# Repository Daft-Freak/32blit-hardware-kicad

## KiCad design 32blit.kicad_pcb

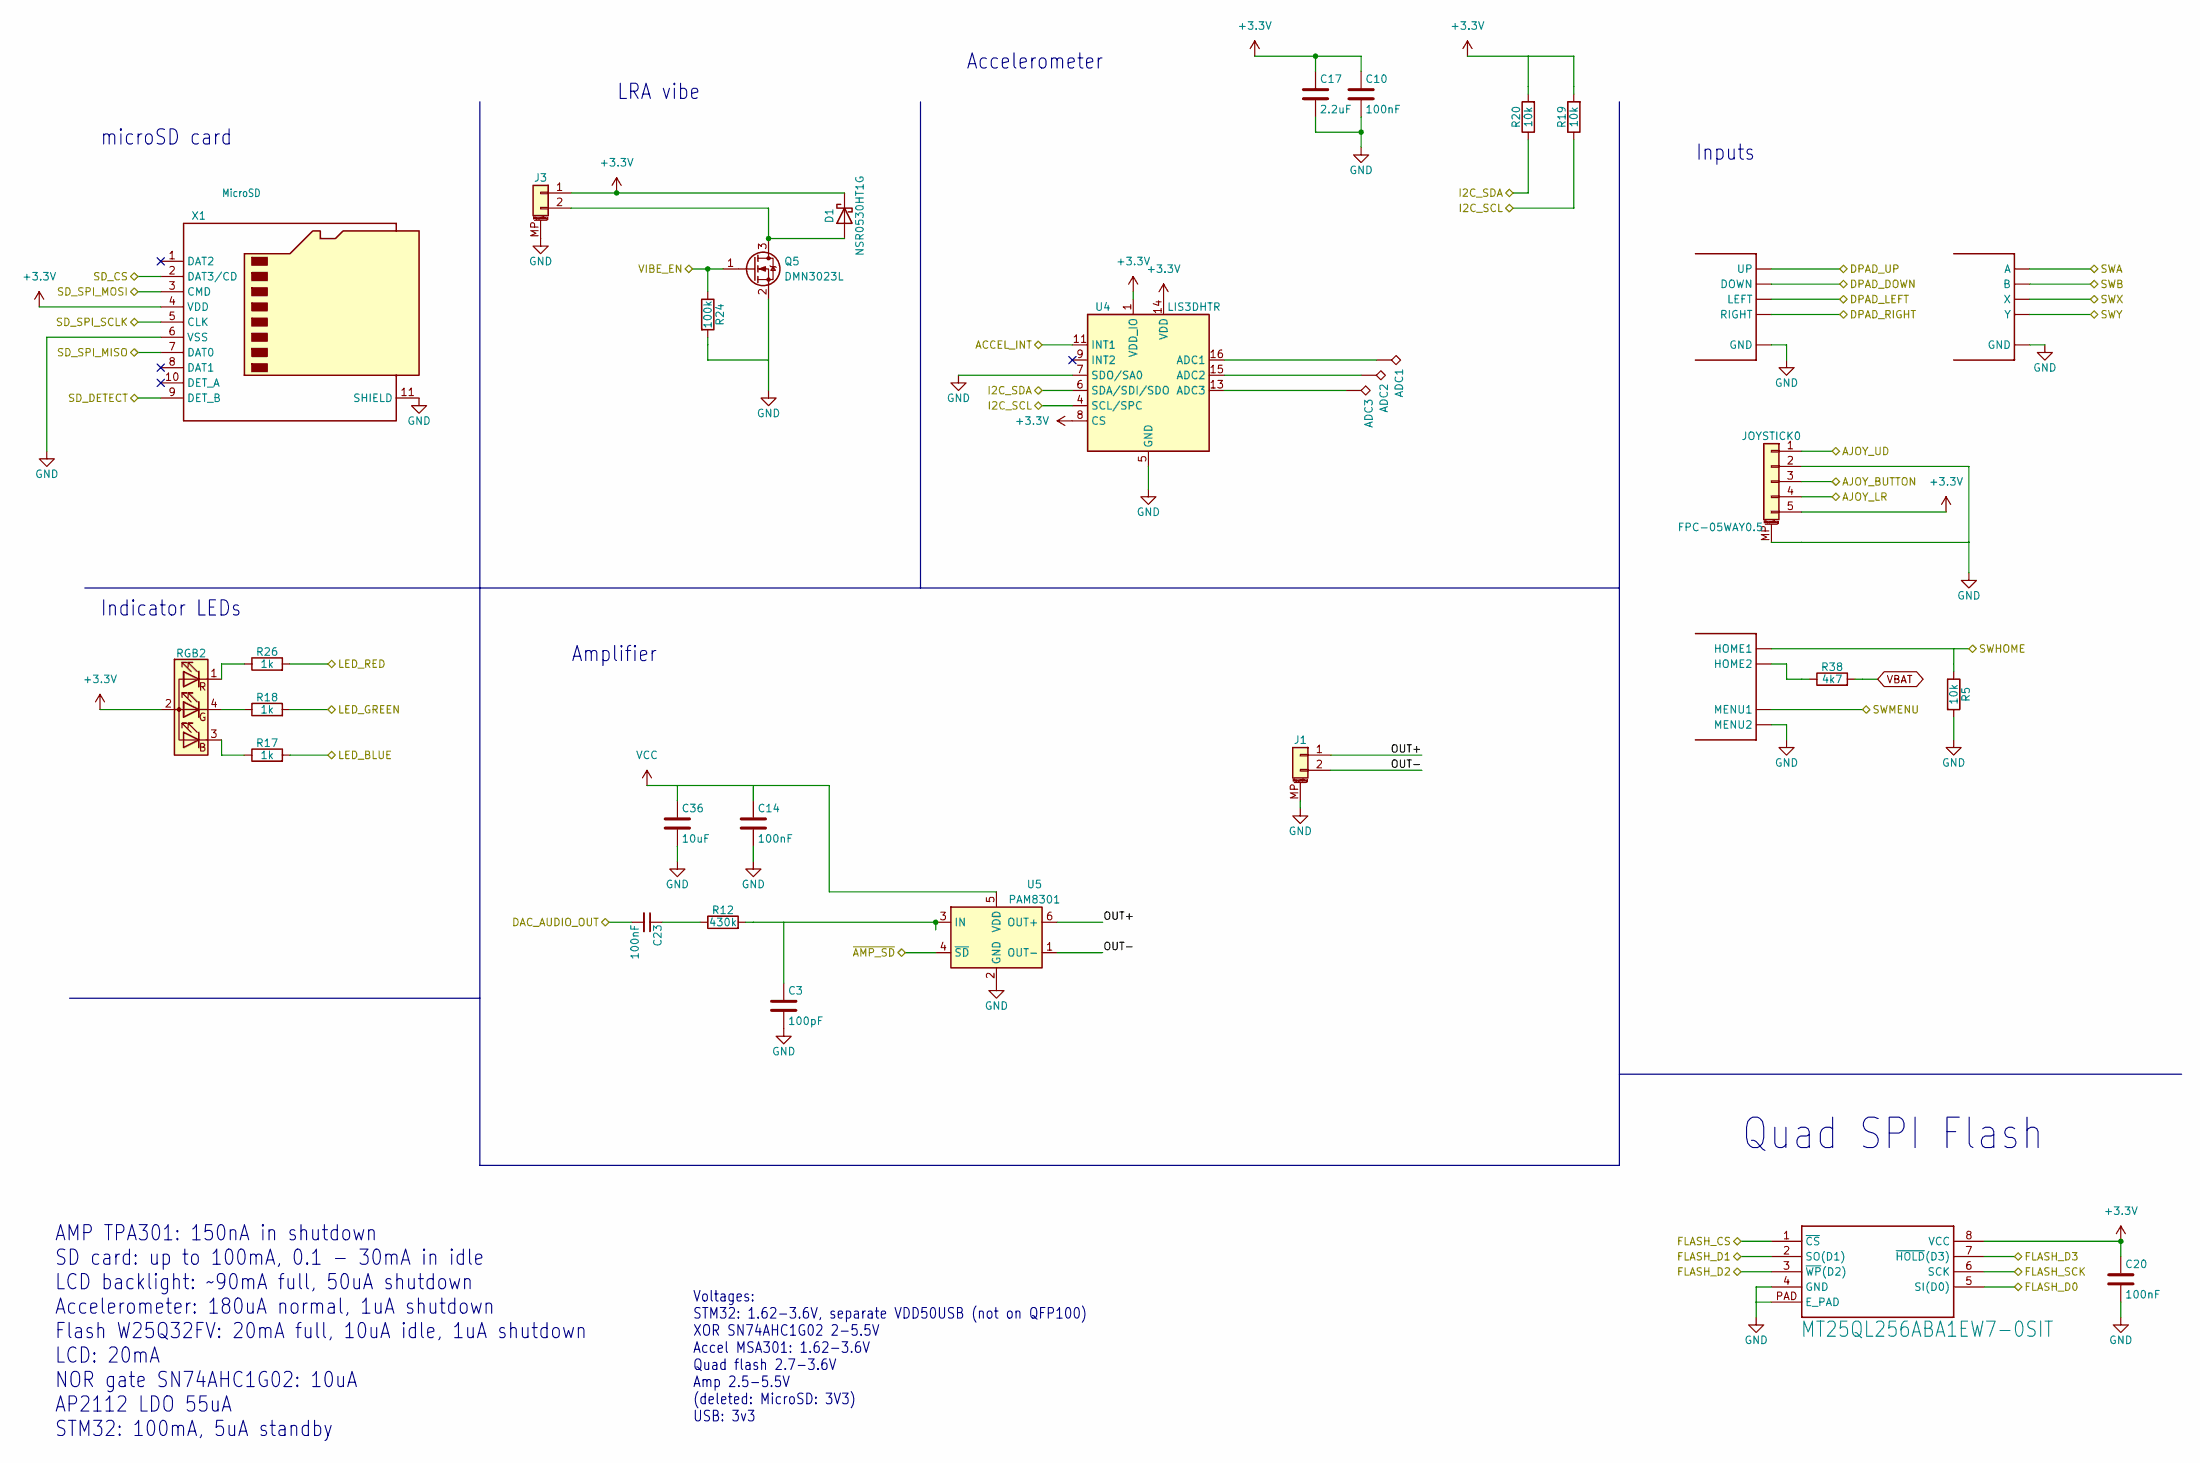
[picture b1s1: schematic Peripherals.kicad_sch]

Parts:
ABXY0: ABXY
ADC1, ADC2, ADC3: TPTP17SQ; TP17SQ
C3: 100pF; C_0603_1608Metric
C10, C14, C20, C23: 100nF; C_0402_1005Metric
C17: 2.2uF; C_0603_1608Metric
C36: 10uF; C_0805_2012Metric
D1: NSR0530HT1G; SOD-323
DPAD0: DPAD
J1: 1X02PICOBLADE; Molex_PicoBlade_53261-0271_1x02-1MP_P1.25mm_Horizontal
J3: 1X02JST_SH; JST_SH_SM02B-SRSS-TB_1x02-1MP_P1.00mm_Horizontal
JOYSTICK0: FPC-05WAY0.5; FPC-0.5MM-05WAY
Q5: DMN3023L; SOT-23
R5, R19, R20: 10k; R_0603_1608Metric
R12: 430k; R_0603_1608Metric
R17, R18, R26: 1k; R_0603_1608Metric
R24: 100k; R_0603_1608Metric
R38: 4k7; R_0603_1608Metric
RGB2: LED_RGB_4P6028_REVERSE; LED-6028_REVERSE_RGB
U4: LIS3DHTR; LGA-16_3x3mm_P0.5mm_LayoutBorder3x5y
U5: PAM8301; SOT-23-6
U22: MT25QL256ABA1EW7-0SIT; DFN-8_6X5MM
U$18: HOME-MENU; MENU-HOME
X1: MicroSD; MICROSD

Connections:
+3.3V: C10.1, C17.1, C20.1, D1.1 (K), J3.1, JOYSTICK0.5, R19.2, R20.2, RGB2.2 (A), U4.1 (VDD_IO), U4.8 (CS), U4.14 (VDD), U22.8 (VCC), X1.4 (VDD); also elsewhere on the board
/I2C_SCL: R19.1, U4.4 (SCL/SPC); also elsewhere on the board
/I2C_SDA: R20.1, U4.6 (SDA/SDI/SDO); also elsewhere on the board
/MCU/ACCEL_INT: U4.11 (INT1); also elsewhere on the board
/MCU/AJOY_BUTTON: JOYSTICK0.3; also elsewhere on the board
/MCU/AJOY_LR: JOYSTICK0.4; also elsewhere on the board
/MCU/AJOY_UD: JOYSTICK0.1; also elsewhere on the board
/MCU/DAC_AUDIO_OUT: C23.2; also elsewhere on the board
/MCU/DPAD_DOWN: DPAD0.DOWN; also elsewhere on the board
/MCU/DPAD_LEFT: DPAD0.LEFT; also elsewhere on the board
/MCU/DPAD_RIGHT: DPAD0.RIGHT; also elsewhere on the board
/MCU/DPAD_UP: DPAD0.UP; also elsewhere on the board
/MCU/FLASH_CS: U22.1 (~CS); also elsewhere on the board
/MCU/FLASH_D0: U22.5 (SI(D0)); also elsewhere on the board
/MCU/FLASH_D1: U22.2 (SO(D1)); also elsewhere on the board
/MCU/FLASH_D2: U22.3 (~WP(D2)); also elsewhere on the board
/MCU/FLASH_D3: U22.7 (~HOLD(D3)); also elsewhere on the board
/MCU/FLASH_SCK: U22.6 (SCK); also elsewhere on the board
/MCU/LED_BLUE: R17.2; also elsewhere on the board
/MCU/LED_GREEN: R18.2; also elsewhere on the board
/MCU/LED_RED: R26.2; also elsewhere on the board
/MCU/SD_CS: X1.2 (DAT3/CD); also elsewhere on the board
/MCU/SD_DETECT: X1.9 (DET_B); also elsewhere on the board
/MCU/SD_SPI_MISO: X1.7 (DAT0); also elsewhere on the board
/MCU/SD_SPI_MOSI: X1.3 (CMD); also elsewhere on the board
/MCU/SD_SPI_SCLK: X1.5 (CLK); also elsewhere on the board
/MCU/SWA: ABXY0.A; also elsewhere on the board
/MCU/SWB: ABXY0.B; also elsewhere on the board
/MCU/SWMENU: U$18.MENU (MENU1); also elsewhere on the board
/MCU/VIBE_EN: Q5.1 (G), R24.1; also elsewhere on the board
/MCU/~AMP_SD: U5.4 (~SD); also elsewhere on the board
/Peripherals/OUT+: J1.1, U5.6 (OUT+)
/Peripherals/OUT-: J1.2, U5.1 (OUT-)
/SWHOME: R5.1, U$18.HOME (HOME1); also elsewhere on the board
GND: ABXY0.GND1 (GND), ABXY0.GND2 (GND), ABXY0.GND3 (GND), ABXY0.GND4 (GND), C3.2, C10.2, C14.2, C17.2, C20.2, C36.2, DPAD0.GND1 (GND), DPAD0.GND2 (GND), DPAD0.GND3 (GND), DPAD0.GND4 (GND), J1.MP (MountPin), J3.MP (MountPin), JOYSTICK0.2, JOYSTICK0.MP (MountPin), Q5.2 (S), R5.2, R24.2, U4.5 (GND), U4.7 (SDO/SA0), U4.10 (GND), U4.12 (GND), U5.2 (GND), U22.4 (GND), U22.PAD (E_PAD), U$18.GND3 (MENU2), X1.6 (VSS), X1.11 (SHIELD); also elsewhere on the board
unnamed: C23.1, R12.1
unnamed: D1.2 (A), J3.2, Q5.3 (D)
unnamed: R17.1, RGB2.3 (BK)
unnamed: R18.1, RGB2.4 (GK)
unnamed: R26.1, RGB2.1 (RK)
unnamed: ADC1.1, U4.16 (ADC1)
unnamed: ADC2.1, U4.15 (ADC2)
unnamed: ADC3.1, U4.13 (ADC3)
unnamed: C3.1, R12.2, U5.3 (IN)
unnamed: R38.1, U$18.GND4 (HOME2)
SWX: ABXY0.X; also elsewhere on the board
SWY: ABXY0.Y; also elsewhere on the board
VBAT: R38.2; also elsewhere on the board
VCC: C14.1, C36.1, U5.5 (VDD); also elsewhere on the board

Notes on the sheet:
Accelerometer
microSD card
Voltages: STM32: 1.62-3.6V, separate VDD50USB (not on QFP100) XOR SN74AHC1G02 2-5.5V Accel MSA301: 1.62-3.6V Quad flash 2.7-3.6V Amp 2.5-5.5V (deleted: MicroSD: 3V3) USB: 3v3
LRA vibe
Amplifier
Quad SPI Flash
Indicator LEDs
AMP TPA301: 150nA in shutdown SD card: up to 100mA, 0.1 - 30mA in idle LCD backlight: ~90mA full, 50uA shutdown Accelerometer: 180uA normal, 1uA shutdown Flash W25Q32FV: 20mA full, 10uA idle, 1uA shutdown LCD: 20mA NOR gate SN74AHC1G02: 10uA AP2112 LDO 55uA STM32: 100mA, 5uA standby
Inputs

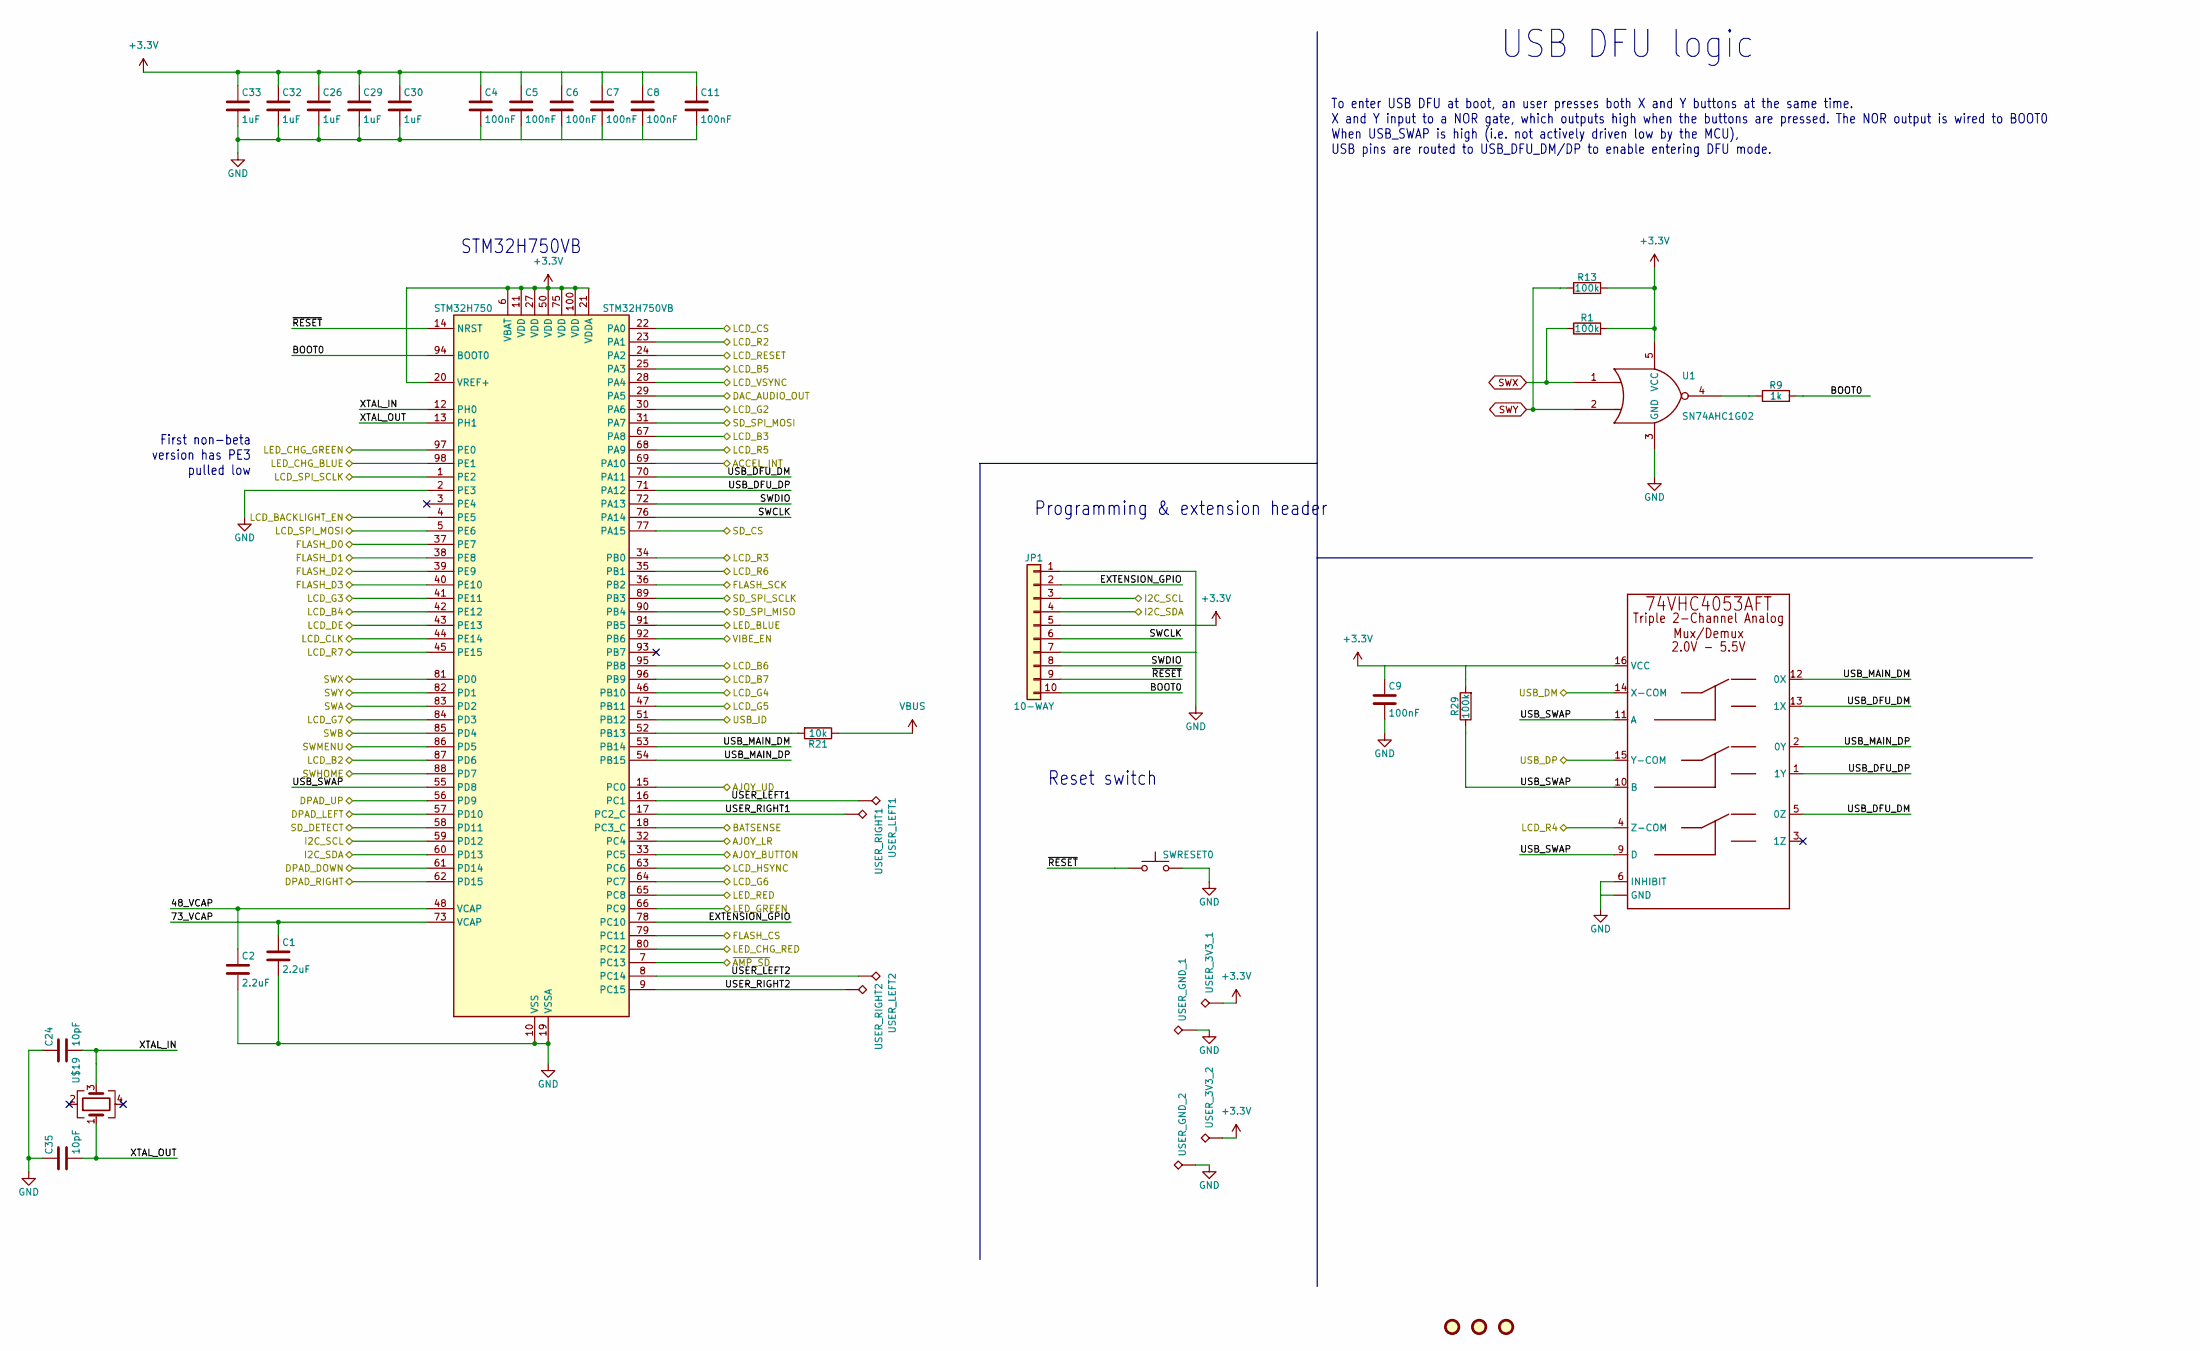
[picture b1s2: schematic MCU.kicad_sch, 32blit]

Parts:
C1, C2: 2.2uF; C_0603_1608Metric
C4, C5, C6, C7, C8, C9, C11: 100nF; C_0402_1005Metric
C24, C35: 10pF; C_0603_1608Metric
C26, C29, C30, C32, C33: 1uF; C_0603_1608Metric
JP1: 10-WAY; 1X10_FEMALE_SMT_RIGHT_ANGLE
R1, R13, R29: 100k; R_0603_1608Metric
R9: 1k; R_0603_1608Metric
R21: 10k; R_0603_1608Metric
STM32H750: STM32H750VB; LQFP-100_14x14mm_P0.5mm
SWRESET0: LY-A03-02; TACT_RIGHT_ANGLE_LOW_PROFILE
U1: SN74AHC1G02; SOT-23-5
U8: 74VHC4053AFT; TSSOP-16_4.4x5mm_P0.65mm
U$17, U$22, U$23: FIDUCIAL1MM; Fiducial_1mm_Mask2mm
U$19: ABM8G-12.000MHZ-4Y-T3; Crystal_SMD_SeikoEpson_TSX3225-4Pin_3.2x2.5mm
USER_3V3_1, USER_3V3_2: TPTP17SQ; TP17SQ
USER_GND_1, USER_GND_2: TPTP17SQ; TP17SQ
USER_LEFT1, USER_LEFT2: TPTP17SQ; TP17SQ
USER_RIGHT1, USER_RIGHT2: TPTP17SQ; TP17SQ

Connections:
+3.3V: C4.1, C5.1, C6.1, C7.1, C8.1, C9.1, C11.1, C26.1, C29.1, C30.1, C32.1, C33.1, JP1.5, R1.2, R13.2, R29.2, STM32H750.6 (VBAT), STM32H750.11 (VDD), STM32H750.20 (VREF+), STM32H750.21 (VDDA), STM32H750.27 (VDD), STM32H750.50 (VDD), STM32H750.75 (VDD), STM32H750.100 (VDD), U1.5 (VCC), U8.16 (VCC), USER_3V3_1.1, USER_3V3_2.1; also elsewhere on the board
/I2C_SCL: JP1.3, STM32H750.59 (PD12); also elsewhere on the board
/I2C_SDA: JP1.4, STM32H750.60 (PD13); also elsewhere on the board
/LCDs and Power/BATSENSE: STM32H750.18 (PC3_C); also elsewhere on the board
/LCDs and Power/LCD_B2: STM32H750.87 (PD6); also elsewhere on the board
/LCDs and Power/LCD_B3: STM32H750.67 (PA8); also elsewhere on the board
/LCDs and Power/LCD_B4: STM32H750.42 (PE12); also elsewhere on the board
/LCDs and Power/LCD_B5: STM32H750.25 (PA3); also elsewhere on the board
/LCDs and Power/LCD_B6: STM32H750.95 (PB8); also elsewhere on the board
/LCDs and Power/LCD_B7: STM32H750.96 (PB9); also elsewhere on the board
/LCDs and Power/LCD_BACKLIGHT_EN: STM32H750.4 (PE5); also elsewhere on the board
/LCDs and Power/LCD_CLK: STM32H750.44 (PE14); also elsewhere on the board
/LCDs and Power/LCD_CS: STM32H750.22 (PA0); also elsewhere on the board
/LCDs and Power/LCD_DE: STM32H750.43 (PE13); also elsewhere on the board
/LCDs and Power/LCD_G2: STM32H750.30 (PA6); also elsewhere on the board
/LCDs and Power/LCD_G3: STM32H750.41 (PE11); also elsewhere on the board
/LCDs and Power/LCD_G4: STM32H750.46 (PB10); also elsewhere on the board
/LCDs and Power/LCD_G5: STM32H750.47 (PB11); also elsewhere on the board
/LCDs and Power/LCD_G6: STM32H750.64 (PC7); also elsewhere on the board
/LCDs and Power/LCD_G7: STM32H750.84 (PD3); also elsewhere on the board
/LCDs and Power/LCD_HSYNC: STM32H750.63 (PC6); also elsewhere on the board
/LCDs and Power/LCD_R2: STM32H750.23 (PA1); also elsewhere on the board
/LCDs and Power/LCD_R3: STM32H750.34 (PB0); also elsewhere on the board
/LCDs and Power/LCD_R4: U8.4 (Z-COM); also elsewhere on the board
/LCDs and Power/LCD_R5: STM32H750.68 (PA9); also elsewhere on the board
/LCDs and Power/LCD_R6: STM32H750.35 (PB1); also elsewhere on the board
/LCDs and Power/LCD_R7: STM32H750.45 (PE15); also elsewhere on the board
/LCDs and Power/LCD_RESET: STM32H750.24 (PA2); also elsewhere on the board
/LCDs and Power/LCD_SPI_MOSI: STM32H750.5 (PE6); also elsewhere on the board
/LCDs and Power/LCD_SPI_SCLK: STM32H750.1 (PE2); also elsewhere on the board
/LCDs and Power/LCD_VSYNC: STM32H750.28 (PA4); also elsewhere on the board
/LCDs and Power/LED_CHG_BLUE: STM32H750.98 (PE1); also elsewhere on the board
/LCDs and Power/LED_CHG_GREEN: STM32H750.97 (PE0); also elsewhere on the board
/LCDs and Power/LED_CHG_RED: STM32H750.80 (PC12); also elsewhere on the board
/LCDs and Power/USB_DM: U8.14 (X-COM); also elsewhere on the board
/LCDs and Power/USB_DP: U8.15 (Y-COM); also elsewhere on the board
/LCDs and Power/USB_ID: STM32H750.51 (PB12); also elsewhere on the board
/MCU/48_VCAP: C2.1, STM32H750.48 (VCAP)
/MCU/73_VCAP: C1.1, STM32H750.73 (VCAP)
/MCU/ACCEL_INT: STM32H750.69 (PA10); also elsewhere on the board
/MCU/AJOY_BUTTON: STM32H750.33 (PC5); also elsewhere on the board
/MCU/AJOY_LR: STM32H750.32 (PC4); also elsewhere on the board
/MCU/AJOY_UD: STM32H750.15 (PC0); also elsewhere on the board
/MCU/BOOT0: JP1.10, R9.2, STM32H750.94 (BOOT0)
/MCU/DAC_AUDIO_OUT: STM32H750.29 (PA5); also elsewhere on the board
/MCU/DPAD_DOWN: STM32H750.61 (PD14); also elsewhere on the board
/MCU/DPAD_LEFT: STM32H750.57 (PD10); also elsewhere on the board
/MCU/DPAD_RIGHT: STM32H750.62 (PD15); also elsewhere on the board
/MCU/DPAD_UP: STM32H750.56 (PD9); also elsewhere on the board
/MCU/EXTENSION_GPIO: JP1.2, STM32H750.78 (PC10)
/MCU/FLASH_CS: STM32H750.79 (PC11); also elsewhere on the board
/MCU/FLASH_D0: STM32H750.37 (PE7); also elsewhere on the board
/MCU/FLASH_D1: STM32H750.38 (PE8); also elsewhere on the board
/MCU/FLASH_D2: STM32H750.39 (PE9); also elsewhere on the board
/MCU/FLASH_D3: STM32H750.40 (PE10); also elsewhere on the board
/MCU/FLASH_SCK: STM32H750.36 (PB2); also elsewhere on the board
/MCU/LED_BLUE: STM32H750.91 (PB5); also elsewhere on the board
/MCU/LED_GREEN: STM32H750.66 (PC9); also elsewhere on the board
/MCU/LED_RED: STM32H750.65 (PC8); also elsewhere on the board
/MCU/SD_CS: STM32H750.77 (PA15); also elsewhere on the board
/MCU/SD_DETECT: STM32H750.58 (PD11); also elsewhere on the board
/MCU/SD_SPI_MISO: STM32H750.90 (PB4); also elsewhere on the board
/MCU/SD_SPI_MOSI: STM32H750.31 (PA7); also elsewhere on the board
/MCU/SD_SPI_SCLK: STM32H750.89 (PB3); also elsewhere on the board
/MCU/SWA: STM32H750.83 (PD2); also elsewhere on the board
/MCU/SWB: STM32H750.85 (PD4); also elsewhere on the board
/MCU/SWCLK: JP1.6, STM32H750.76 (PA14)
/MCU/SWDIO: JP1.8, STM32H750.72 (PA13)
/MCU/SWMENU: STM32H750.86 (PD5); also elsewhere on the board
/MCU/USB_DFU_DM: STM32H750.70 (PA11), U8.5 (0Z), U8.13 (1X)
/MCU/USB_DFU_DP: STM32H750.71 (PA12), U8.1 (1Y)
/MCU/USB_MAIN_DM: STM32H750.53 (PB14), U8.12 (0X)
/MCU/USB_MAIN_DP: STM32H750.54 (PB15), U8.2 (0Y)
/MCU/USB_SWAP: R29.1, STM32H750.55 (PD8), U8.9 (D), U8.10 (B), U8.11 (A)
/MCU/USER_LEFT1: STM32H750.16 (PC1), USER_LEFT1.1
/MCU/USER_LEFT2: STM32H750.8 (PC14), USER_LEFT2.1
/MCU/USER_RIGHT1: STM32H750.17 (PC2_C), USER_RIGHT1.1
/MCU/USER_RIGHT2: STM32H750.9 (PC15), USER_RIGHT2.1
/MCU/VIBE_EN: STM32H750.92 (PB6); also elsewhere on the board
/MCU/XTAL_IN: C24.2, STM32H750.12 (PH0), U$19.3
/MCU/XTAL_OUT: C35.2, STM32H750.13 (PH1), U$19.1
/MCU/~AMP_SD: STM32H750.7 (PC13); also elsewhere on the board
/MCU/~RESET: JP1.9, STM32H750.14 (NRST), SWRESET0.1
/SWHOME: STM32H750.88 (PD7); also elsewhere on the board
GND: C1.2, C2.2, C4.2, C5.2, C6.2, C7.2, C8.2, C9.2, C11.2, C24.1, C26.2, C29.2, C30.2, C32.2, C33.2, C35.1, JP1.1, JP1.7, STM32H750.2 (PE3), STM32H750.10 (VSS), STM32H750.19 (VSSA), STM32H750.26 (VSS), STM32H750.49 (VSS), STM32H750.74 (VSS), STM32H750.99 (VSS), SWRESET0.2, U1.3 (GND), U8.6 (INHIBIT), U8.7 (GND), U8.8 (GND), USER_GND_1.1, USER_GND_2.1; also elsewhere on the board
unnamed: R9.1, U1.4
unnamed: R21.2, STM32H750.52 (PB13)
SWX: R1.1, STM32H750.81 (PD0), U1.1; also elsewhere on the board
SWY: R13.1, STM32H750.82 (PD1), U1.2; also elsewhere on the board
VBUS: R21.1; also elsewhere on the board

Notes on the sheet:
STM32H750VB
USB DFU logic
Reset switch
Programming & extension header
To enter USB DFU at boot, an user presses both X and Y buttons at the same time. X and Y input to a NOR gate, which outputs high when the buttons are pressed. The NOR output is wired to BOOT0 When USB_SWAP is high (i.e. not actively driven low by the MCU), USB pins are routed to USB_DFU_DM/DP to en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
First non-beta version has PE3 pulled low

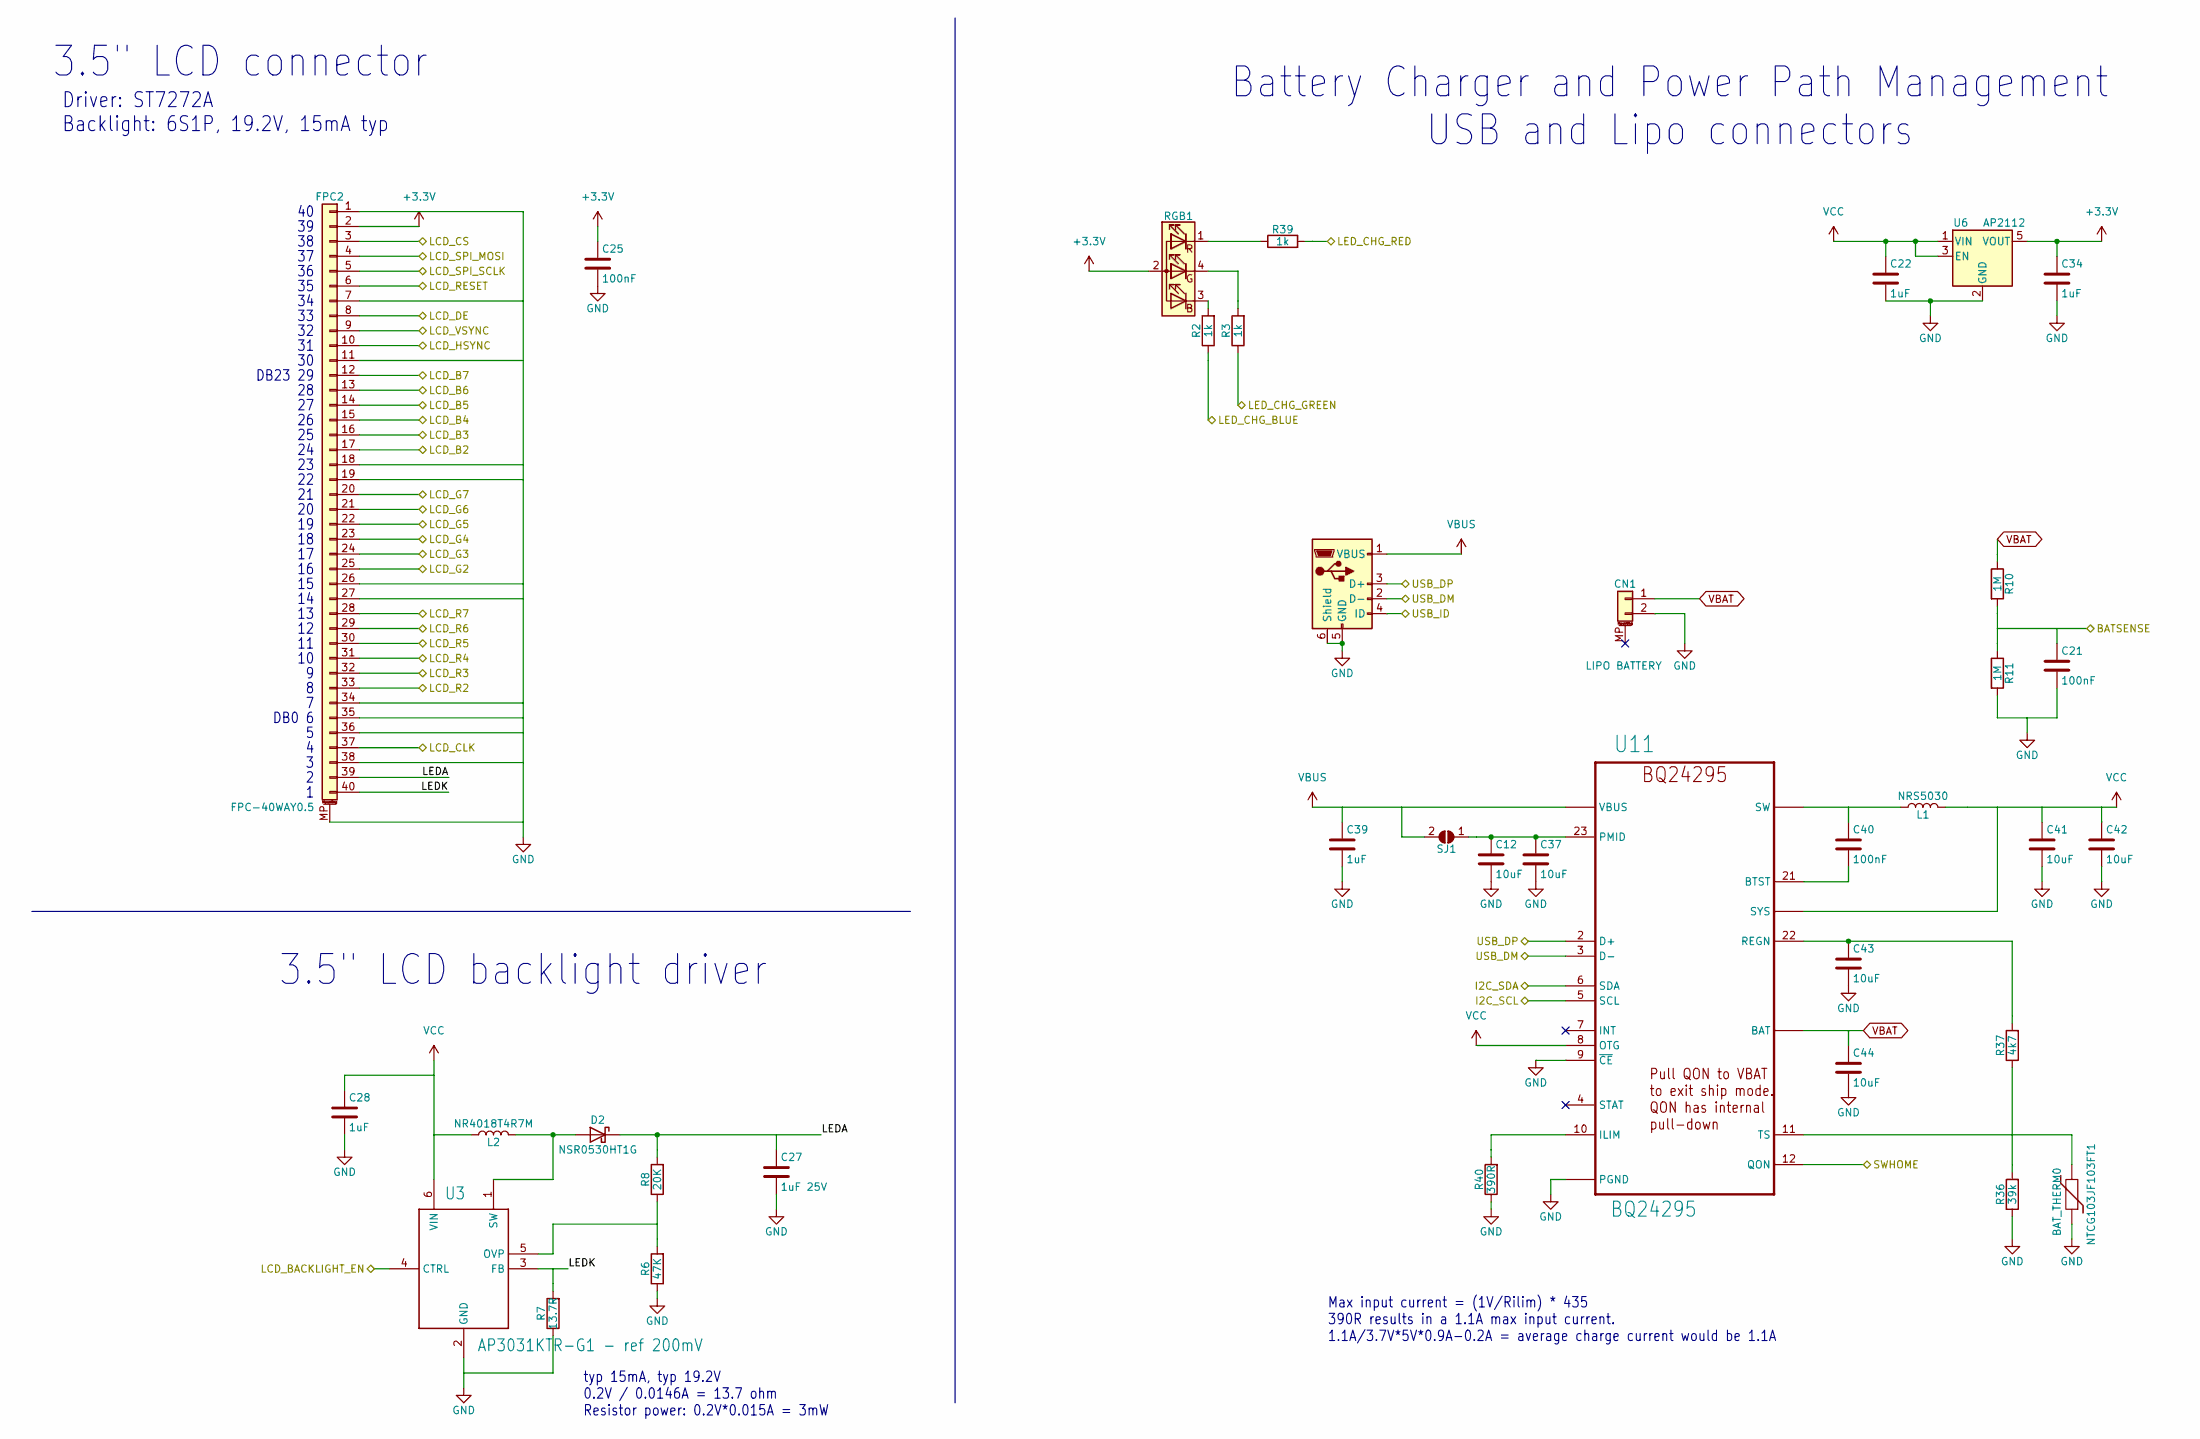
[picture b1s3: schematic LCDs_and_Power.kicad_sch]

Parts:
BAT_THERM0: NTCG103JF103FT1; R_0402_1005Metric
C12, C37, C41, C42, C43, C44: 10uF; C_0805_2012Metric
C21, C25, C40: 100nF; C_0402_1005Metric
C22, C28, C34, C39: 1uF; C_0603_1608Metric
C27: 1uF 25V; C_0603_1608Metric
CN1: LIPO BATTERY; JST_PH_S2B-PH-SM4-TB_1x02-1MP_P2.00mm_Horizontal
D2: NSR0530HT1G
FPC2: FPC-40WAY0.5; FPC-0.5MM-40WAY
L1: NRS5030; L_Taiyo-Yuden_NR-50xx
L2: NR4018T4R7M; L_Taiyo-Yuden_NR-40xx
R2, R3, R39: 1k; R_0603_1608Metric
R6: 47K; R_0603_1608Metric
R7: 13.7R; R_0603_1608Metric
R8: 20K; R_0603_1608Metric
R10, R11: 1M; R_0603_1608Metric
R36: 39k; R_0603_1608Metric
R37: 4k7; R_0603_1608Metric
R40: 390R; R_0603_1608Metric
RGB1: LED_RGB_4P6028_REVERSE; LED-6028_REVERSE_RGB
SJ1: SOLDERJUMPER; SOLDERJUMPER_ARROW_NOPASTE
U3: AP3031KTR-G1 - ref 200mV; SOT-23-6
U6: AP2112; SOT-23-5
U11: BQ24295; QFN50P400X400X100-25N
U$3: USBMICROB; MICROB-USB

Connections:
+3.3V: C25.1, C34.1, FPC2.2, RGB1.2 (A), U6.5 (VOUT); also elsewhere on the board
/I2C_SCL: U11.5 (SCL); also elsewhere on the board
/I2C_SDA: U11.6 (SDA); also elsewhere on the board
/LCDs and Power/BATSENSE: C21.1, R10.2, R11.1; also elsewhere on the board
/LCDs and Power/LCD_B2: FPC2.17; also elsewhere on the board
/LCDs and Power/LCD_B3: FPC2.16; also elsewhere on the board
/LCDs and Power/LCD_B4: FPC2.15; also elsewhere on the board
/LCDs and Power/LCD_B5: FPC2.14; also elsewhere on the board
/LCDs and Power/LCD_B6: FPC2.13; also elsewhere on the board
/LCDs and Power/LCD_B7: FPC2.12; also elsewhere on the board
/LCDs and Power/LCD_BACKLIGHT_EN: U3.4 (CTRL); also elsewhere on the board
/LCDs and Power/LCD_CLK: FPC2.37; also elsewhere on the board
/LCDs and Power/LCD_CS: FPC2.3; also elsewhere on the board
/LCDs and Power/LCD_DE: FPC2.8; also elsewhere on the board
/LCDs and Power/LCD_G2: FPC2.25; also elsewhere on the board
/LCDs and Power/LCD_G3: FPC2.24; also elsewhere on the board
/LCDs and Power/LCD_G4: FPC2.23; also elsewhere on the board
/LCDs and Power/LCD_G5: FPC2.22; also elsewhere on the board
/LCDs and Power/LCD_G6: FPC2.21; also elsewhere on the board
/LCDs and Power/LCD_G7: FPC2.20; also elsewhere on the board
/LCDs and Power/LCD_HSYNC: FPC2.10; also elsewhere on the board
/LCDs and Power/LCD_R2: FPC2.33; also elsewhere on the board
/LCDs and Power/LCD_R3: FPC2.32; also elsewhere on the board
/LCDs and Power/LCD_R4: FPC2.31; also elsewhere on the board
/LCDs and Power/LCD_R5: FPC2.30; also elsewhere on the board
/LCDs and Power/LCD_R6: FPC2.29; also elsewhere on the board
/LCDs and Power/LCD_R7: FPC2.28; also elsewhere on the board
/LCDs and Power/LCD_RESET: FPC2.6; also elsewhere on the board
/LCDs and Power/LCD_SPI_MOSI: FPC2.4; also elsewhere on the board
/LCDs and Power/LCD_SPI_SCLK: FPC2.5; also elsewhere on the board
/LCDs and Power/LCD_VSYNC: FPC2.9; also elsewhere on the board
/LCDs and Power/LEDA: C27.1, D2.1 (K), FPC2.39, R8.2
/LCDs and Power/LEDK: FPC2.40, R7.2, U3.3 (FB)
/LCDs and Power/LED_CHG_BLUE: R2.1; also elsewhere on the board
/LCDs and Power/LED_CHG_GREEN: R3.1; also elsewhere on the board
/LCDs and Power/LED_CHG_RED: R39.2; also elsewhere on the board
/LCDs and Power/USB_DM: U11.3 (D-), U$3.2 (D-); also elsewhere on the board
/LCDs and Power/USB_DP: U11.2 (D+), U$3.3 (D+); also elsewhere on the board
/LCDs and Power/USB_ID: U$3.4 (ID); also elsewhere on the board
/SWHOME: U11.12 (QON); also elsewhere on the board
GND: BAT_THERM0.1, C12.2, C21.2, C22.2, C25.2, C27.2, C28.2, C34.2, C37.2, C39.2, C41.2, C42.2, C43.2, C44.2, CN1.2, FPC2.1, FPC2.7, FPC2.11, FPC2.18, FPC2.19, FPC2.26, FPC2.27, FPC2.34, FPC2.35, FPC2.36, FPC2.38, FPC2.MP (MountPin), R6.1, R7.1, R11.2, R36.1, R40.1, U3.2 (GND), U6.2 (GND), U11.9 (~CE), U11.17 (PGND), U11.18 (PGND), U11.25 (PGND), U$3.5 (GND), U$3.6 (Shield); also elsewhere on the board
unnamed: C40.1, L1.1, U11.19 (SW), U11.20 (SW)
unnamed: D2.2 (A), L2.2, U3.1 (SW)
unnamed: R2.2, RGB1.3 (BK)
unnamed: R3.2, RGB1.4 (GK)
unnamed: R39.1, RGB1.1 (RK)
unnamed: C12.1, C37.1, SJ1.1 (A), U11.23 (PMID)
unnamed: R6.2, R8.1, U3.5 (OVP)
unnamed: C40.2, U11.21 (BTST)
unnamed: R40.2, U11.10 (ILIM)
unnamed: C43.1, R37.2, U11.22 (REGN)
unnamed: BAT_THERM0.2, R36.2, R37.1, U11.11 (TS)
VBAT: C44.1, CN1.1, R10.1, U11.13 (BAT), U11.14 (BAT); also elsewhere on the board
VBUS: C39.1, SJ1.2 (B), U11.1 (VBUS), U11.24 (VBUS), U$3.1 (VBUS); also elsewhere on the board
VCC: C22.1, C28.1, C41.1, C42.1, L1.2, L2.1, U3.6 (VIN), U6.1 (VIN), U6.3 (EN), U11.8 (OTG), U11.15 (SYS), U11.16 (SYS); also elsewhere on the board

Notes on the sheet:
DB0 6
Max input current = (1V/Rilim) * 435 390R results in a 1.1A max input current. 1.1A/3.7V*5V*0.9A-0.2A = average charge current would be 1.1A
DB23 29
Battery Charger and Power Path Management USB and Lipo connectors
Driver: ST7272A Backlight: 6S1P, 19.2V, 15mA typ
3.5" LCD backlight driver
typ 15mA, typ 19.2V 0.2V / 0.0146A = 13.7 ohm Resistor power: 0.2V*0.015A = 3mW
3.5" LCD connector

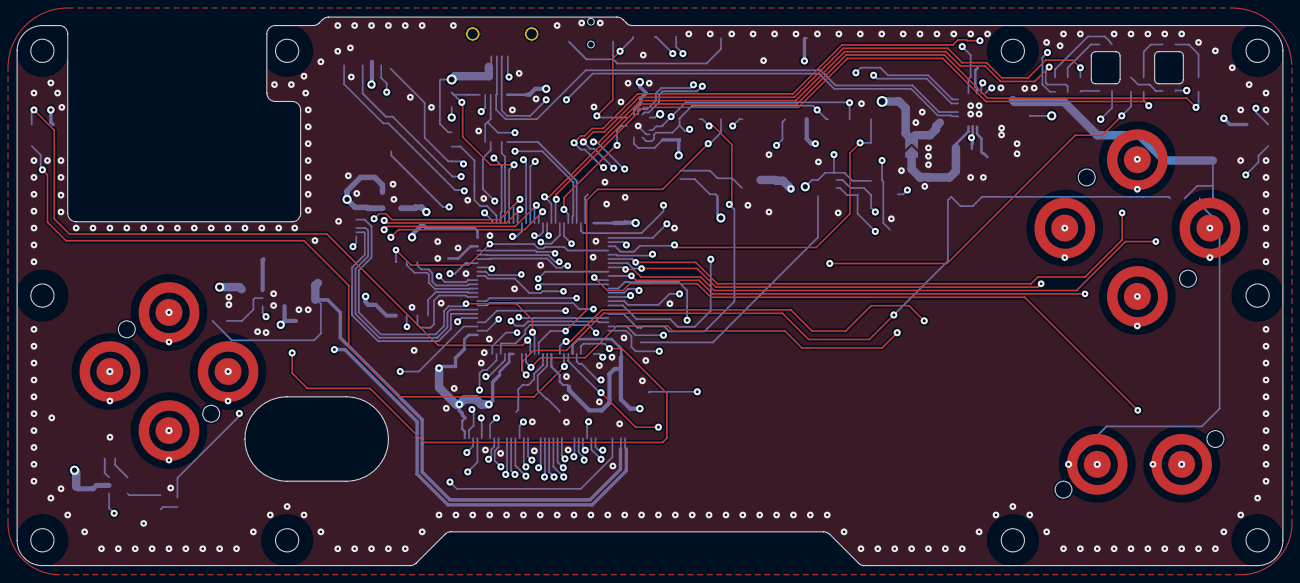
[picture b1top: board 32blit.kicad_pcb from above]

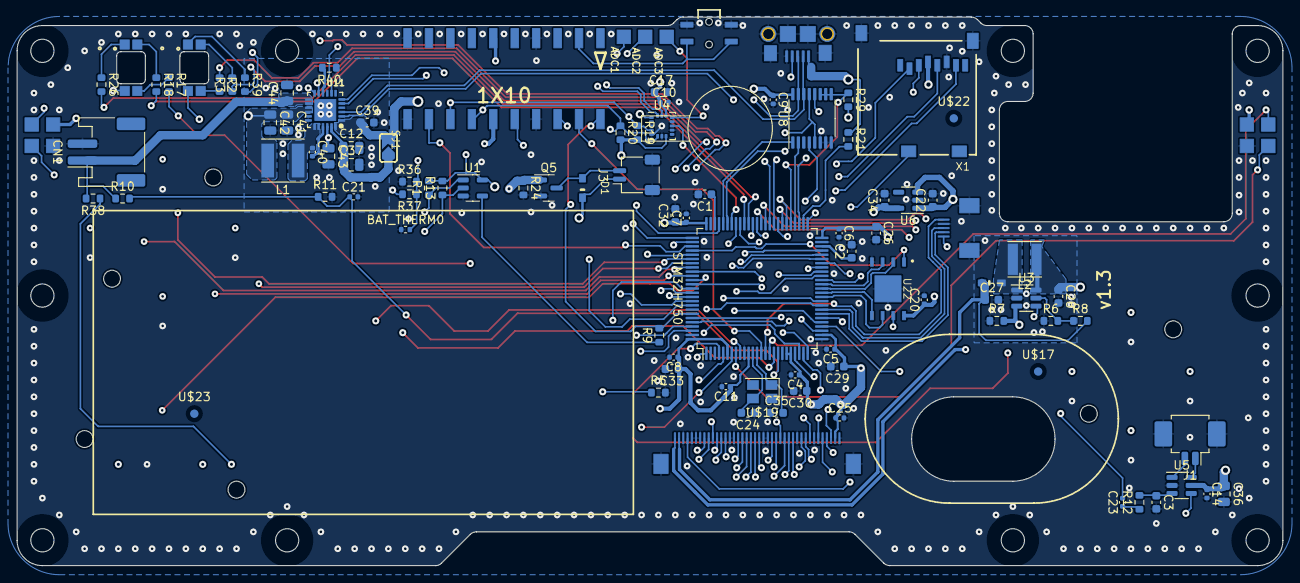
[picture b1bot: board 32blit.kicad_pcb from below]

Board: 4 copper layers, 150.0 x 65.0 mm, 121 parts (106 on the bottom side), 117 nets.

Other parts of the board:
U$2: LRA_ELV1030AC1
U$6, U$8, U$9, U$10, U$11, U$12, U$13, U$14, U$16, U$20: 2.7MM-MOUNTING-HOLE
U$7: LCD_035
U$15: 3020_SPEAKER
U$21: JOYSTICK_ANALOG

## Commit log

2023-12-01 Initial kicad import
2023-12-01 Try to fix button footprints
2023-12-01 Update PCB from schematic
2023-12-01 Use kicad footprints for resistors/capacitors
2023-12-01 More footprint replacements
    This involved some adjusting for pad sizes
2023-12-01 Replace speaker/vibration connector footprints
2023-12-02 Remove custom pimoroni frame
    Makes the sch a bit hard to work with and recreating it in the .kicad_wks seems difficult
2023-12-03 Giant schematic rework
    Use as many kicad symbols as possiblem, adjust remaining imported symbols to make ERC happy and adjust some footprints for the new symbols
2023-12-03 Some board/footprint fixes
    The holes were violating their own keepout. Also adjust some clearances and move a few capacitors a little
